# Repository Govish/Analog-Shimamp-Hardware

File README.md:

# Analog Shimamp Hardware
 Hardware and hardware prototypes for a shim amplifier with analog current control

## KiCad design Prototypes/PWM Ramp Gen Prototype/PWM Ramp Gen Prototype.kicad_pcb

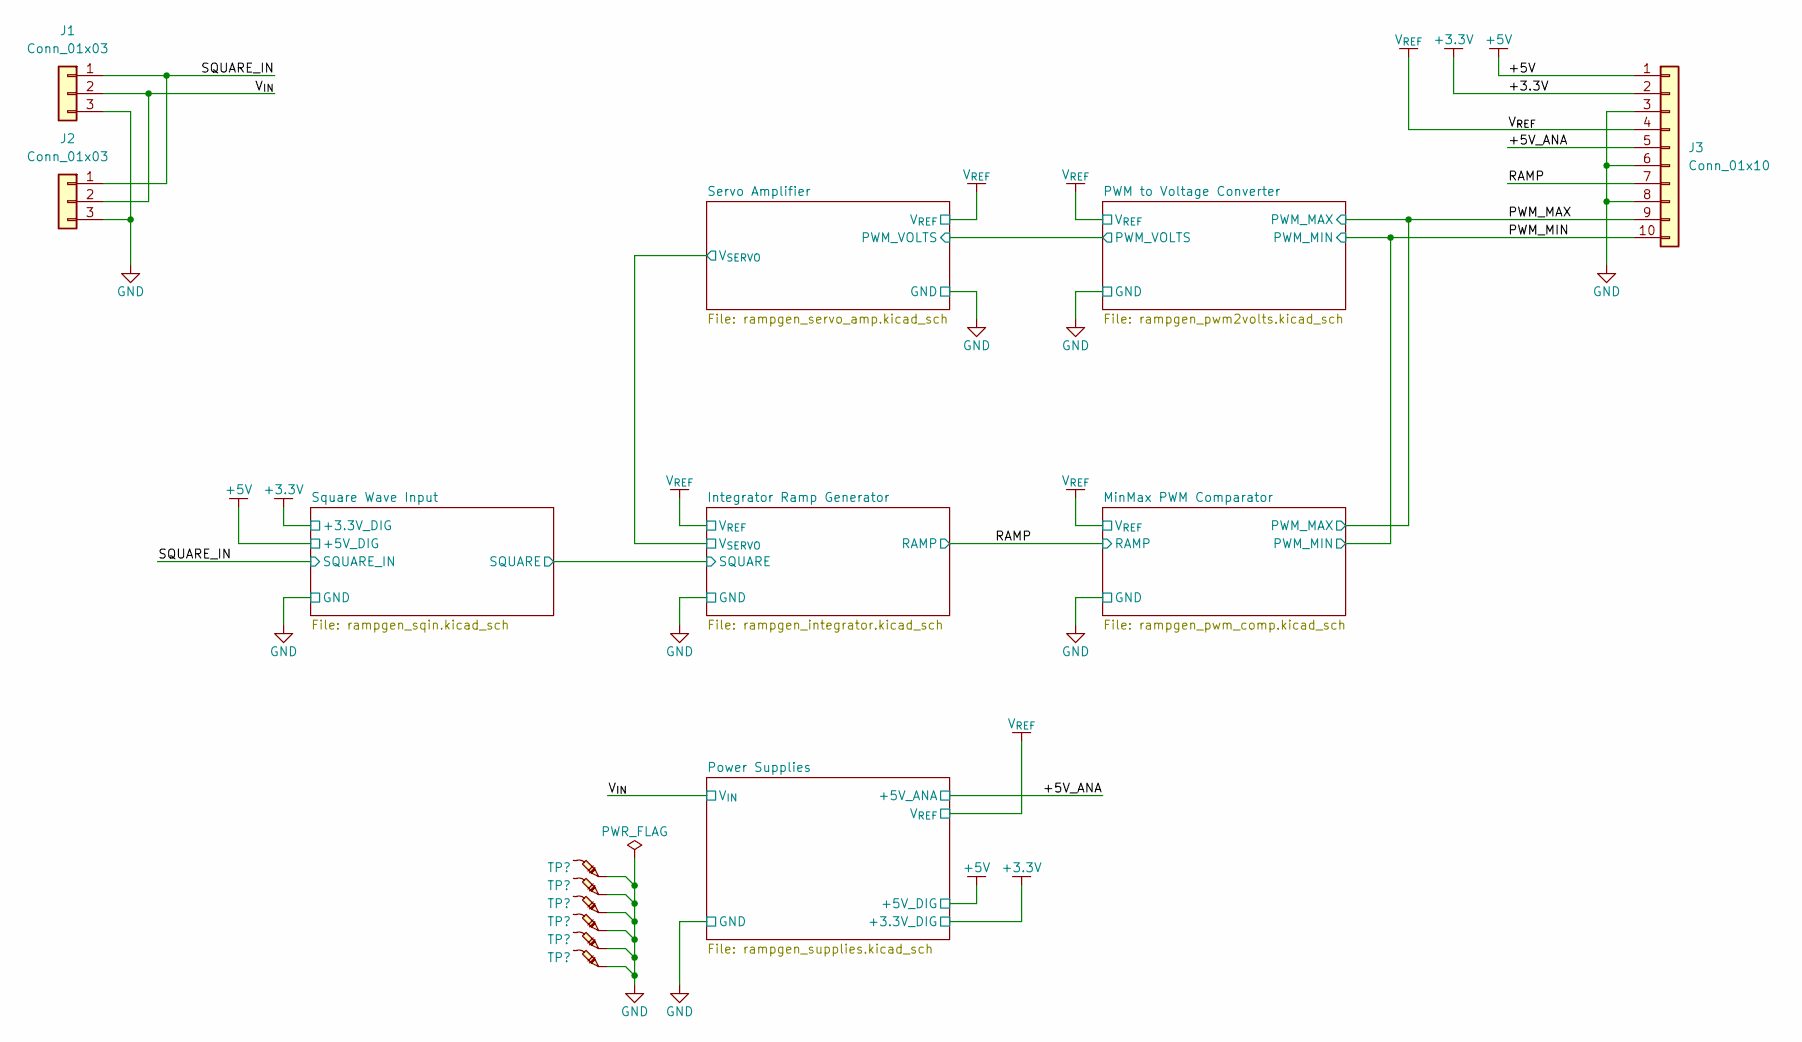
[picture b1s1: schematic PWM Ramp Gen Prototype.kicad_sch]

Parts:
J1, J2: Conn_01x03; PinHeader_1x03_P2.54mm_Vertical
J3: Conn_01x10; PinHeader_1x10_P2.54mm_Vertical
TP1, TP2, TP3, TP4, TP6, TP7: -; TestPoint_Pad_D2.0mm

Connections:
+3.3V: J3.2; also elsewhere on the board
+5V: J3.1; also elsewhere on the board
/+5V_ANA: J3.5; also elsewhere on the board
/PWM_MAX: J3.9; also elsewhere on the board
/PWM_MIN: J3.10; also elsewhere on the board
/RAMP: J3.7; also elsewhere on the board
/SQUARE_IN: J1.1, J2.1; also elsewhere on the board
/V_{IN}: J1.2, J2.2; also elsewhere on the board
GND: J1.3, J2.3, J3.3, J3.6, J3.8, TP1.1, TP2.1, TP3.1, TP4.1, TP6.1, TP7.1; also elsewhere on the board
V_{REF}: J3.4; also elsewhere on the board

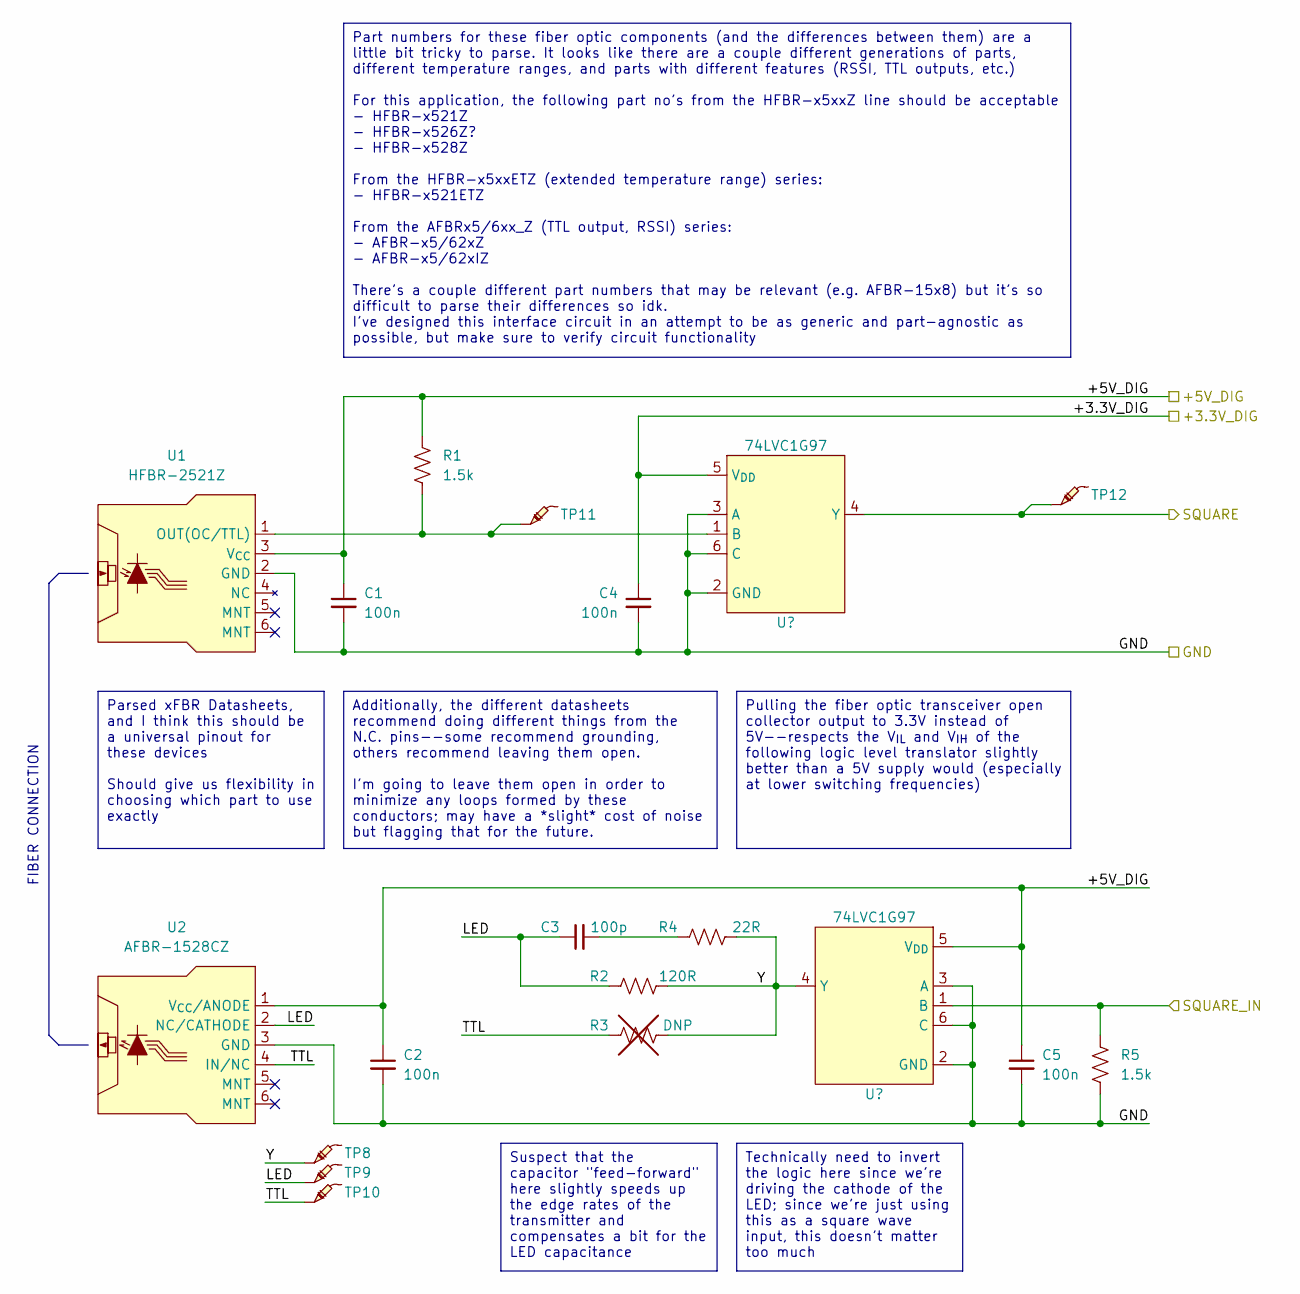
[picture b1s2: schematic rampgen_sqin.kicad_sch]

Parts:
C1, C2, C4, C5: 100n; C_0603_1608Metric_Pad1.08x0.95mm_HandSolder; Part Number CL10B104KB8NNWC
C3: 100p; C_0603_1608Metric_Pad1.08x0.95mm_HandSolder; Part Number GCM1885C2A101JA16D
R1, R5: 1.5k; R_0603_1608Metric_Pad0.98x0.95mm_HandSolder; Part Number RMCF0603FT1K50
R2: 120R; R_0603_1608Metric_Pad0.98x0.95mm_HandSolder; Part Number RMCF0603FT120R
R3: DNP; DNP_R_0603_1608Metric_Pad0.98x0.95mm_HandSolder
R4: 22R; R_0603_1608Metric_Pad0.98x0.95mm_HandSolder; Part Number RMCF0603FT22R0
TP8, TP9, TP10, TP11, TP12: -; TestPoint_Pad_D2.0mm
U1: HFBR-2521Z; Broadcom_xFBR_RX; Part Number HFBR-2521Z
U2: AFBR-1528CZ; Broadcom_xFBR_TX; Part Number AFBR-1528CZ
U3, U4: 74LVC1G97; SOT-363_SC-70-6_Handsoldering; Part Number 74LVC1G97GW,125

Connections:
+3.3V: C4.1, U3.5 (V_{DD}); also elsewhere on the board
+5V: C1.1, C2.1, C5.1, R1.1, U1.3 (V_{CC}), U2.1 (V_{CC}/ANODE), U4.5 (V_{DD}); also elsewhere on the board
/Integrator Ramp Generator/SQUARE: TP12.1, U3.4 (Y); also elsewhere on the board
/SQUARE_IN: R5.1, U4.1 (B); also elsewhere on the board
/Square Wave Input/LED: C3.1, R2.1, TP9.1, U2.2 (NC/CATHODE)
/Square Wave Input/TTL: R3.1, TP10.1, U2.4 (IN/NC)
/Square Wave Input/Y: R2.2, R3.2, R4.2, TP8.1, U4.4 (Y)
GND: C1.2, C2.2, C4.2, C5.2, R5.2, U1.2 (GND), U2.3 (GND), U3.2 (GND), U3.3 (A), U3.6 (C), U4.2 (GND), U4.3 (A), U4.6 (C); also elsewhere on the board
unnamed: C3.2, R4.1
unnamed: R1.2, TP11.1, U1.1 (OUT(OC/TTL)), U3.1 (B)

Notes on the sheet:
Parsed xFBR Datasheets, and I think this should be a universal pinout for these devices Should give us flexibility in choosing which part to use exactly
Part numbers for these fiber optic components (and the differences between them) are a little bit tricky to parse. It looks like there are a couple different generations of parts, different temperature ranges, and parts with different features (RSSI, TTL outputs, etc.) For this application, the fol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
Additionally, the different datasheets recommend doing different things from the N.C. pins--some recommend grounding, others recommend leaving them open. I'm going to leave them open in order to minimize any loops formed by these conductors; may have a *slight* cost of noise but flagging that for t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
Technically need to invert the logic here since we're driving the cathode of the LED; since we're just using this as a square wave input, this doesn't matter too much
Suspect that the capacitor "feed-forward" here slightly speeds up the edge rates of the transmitter and compensates a bit for the LED capacitance
Pulling the fiber optic transceiver open collector output to 3.3V instead of 5V--respects the V_{IL} and V_{IH} of the following logic level translator slightly better than a 5V supply would (especially at lower switching frequencies)
FIBER CONNECTION

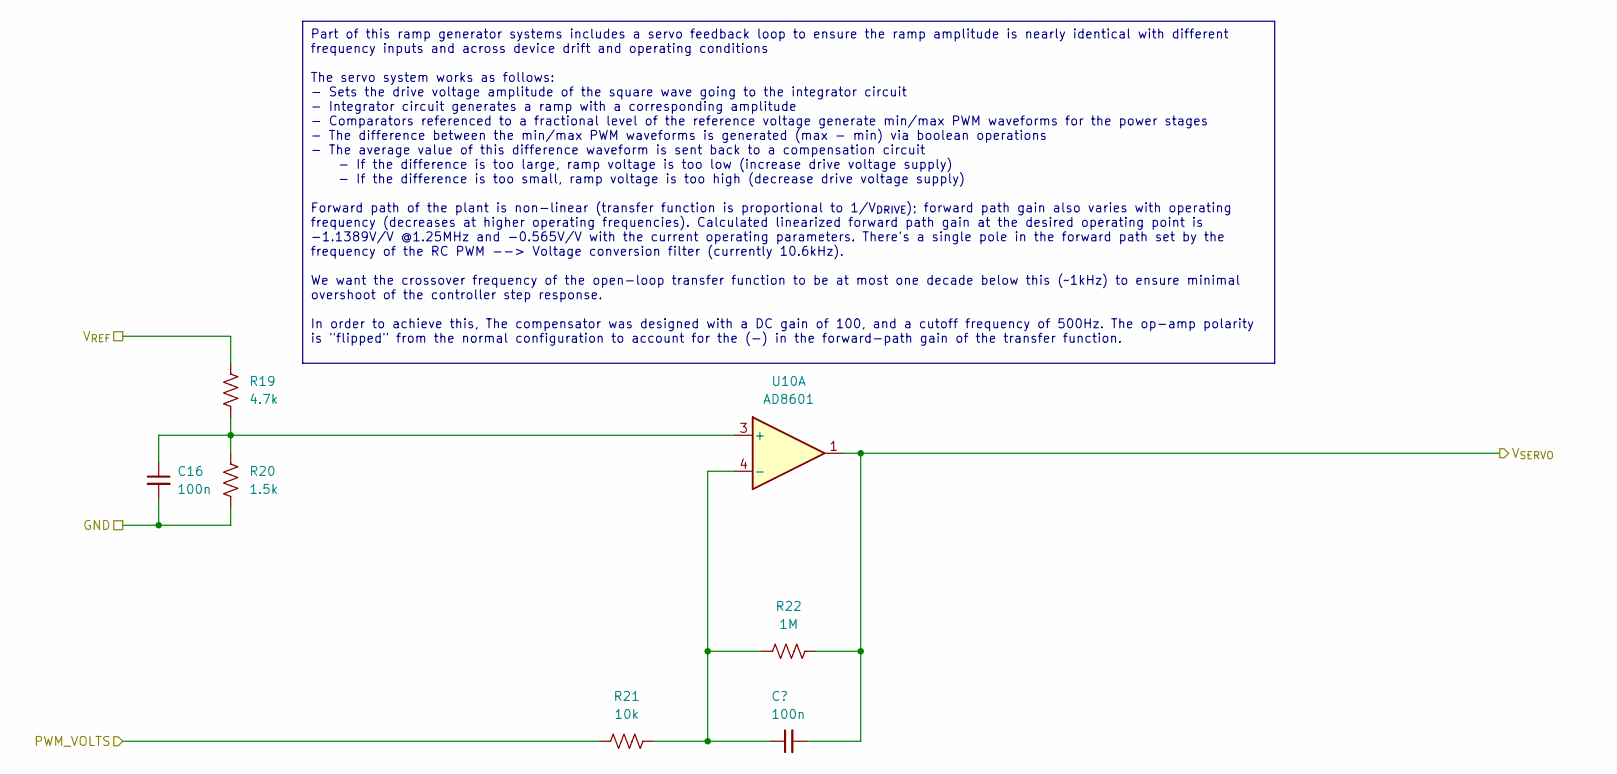
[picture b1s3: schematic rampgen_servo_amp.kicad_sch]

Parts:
C16, C17: 100n; C_0603_1608Metric_Pad1.08x0.95mm_HandSolder; Part Number CL10B104KB8NNWC
R19: 4.7k; R_0603_1608Metric_Pad0.98x0.95mm_HandSolder; Part Number RMCF0603FT4K70
R20: 1.5k; R_0603_1608Metric_Pad0.98x0.95mm_HandSolder; Part Number RMCF0603FT1K50
R21: 10k; R_0603_1608Metric_Pad0.98x0.95mm_HandSolder; Part Number RMCF0603FT10K0
R22: 1M; R_0603_1608Metric_Pad0.98x0.95mm_HandSolder; Part Number RMCF0603FT1M00
U10: AD8601; SOT-23-6_Handsoldering; Part Number AD8601WDRTZ-REEL7

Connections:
/Integrator Ramp Generator/V_{SERVO}: C17.2, R22.2, U10.1; also elsewhere on the board
/PWM to Voltage Converter/PWM_VOLTS: R21.1; also elsewhere on the board
GND: C16.2, R20.2; also elsewhere on the board
unnamed: C16.1, R19.2, R20.1, U10.3 (+)
unnamed: C17.1, R21.2, R22.1, U10.4 (-)
V_{REF}: R19.1; also elsewhere on the board

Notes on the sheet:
Part of this ramp generator systems includes a servo feedback loop to ensure the ramp amplitude is nearly identical with different frequency inputs and across device drift and operating conditions The servo system works as follows: - Sets the drive voltage amplitude of the square wave going to the 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

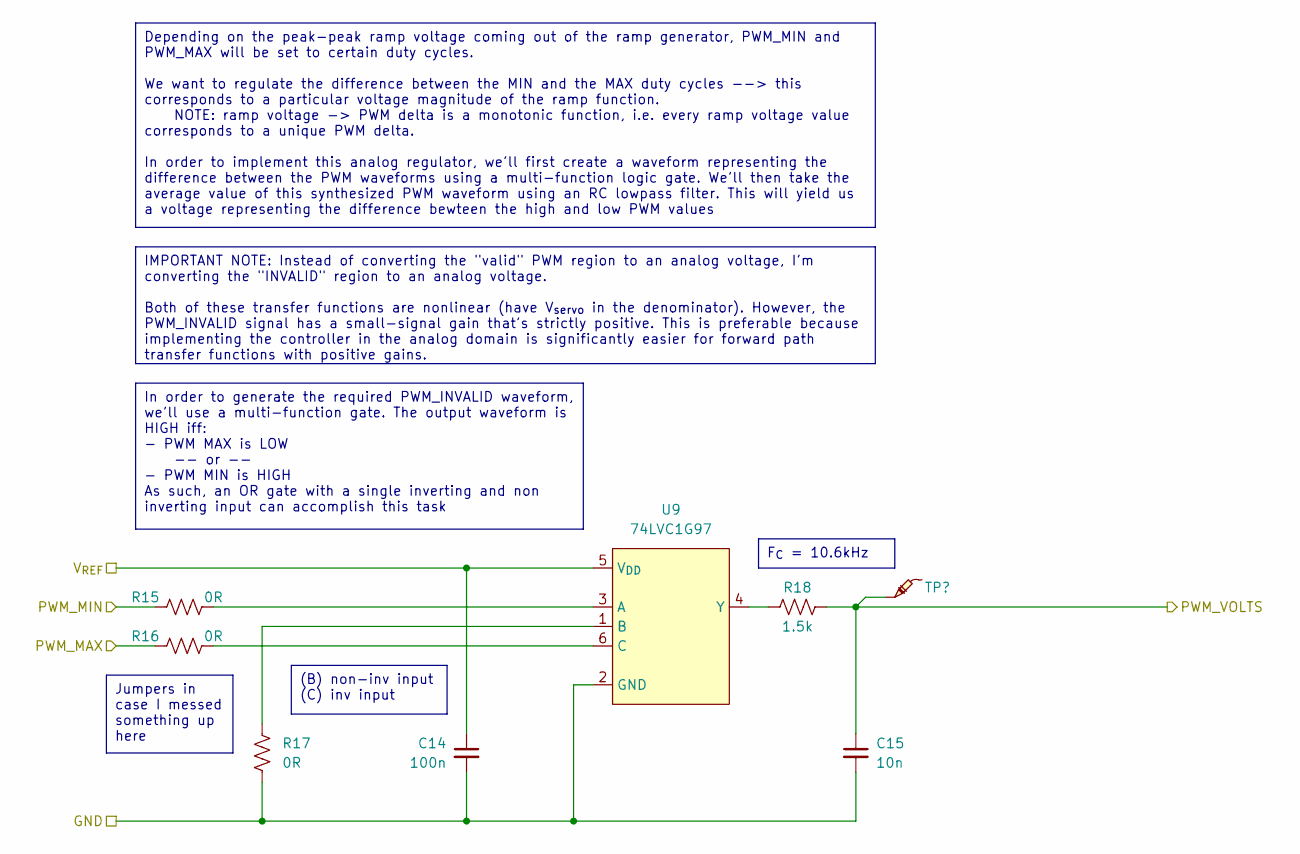
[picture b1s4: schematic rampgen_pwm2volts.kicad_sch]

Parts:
C14: 100n; C_0603_1608Metric_Pad1.08x0.95mm_HandSolder; Part Number CL10B104KB8NNWC
C15: 10n; C_0603_1608Metric_Pad1.08x0.95mm_HandSolder; Part Number CL10B103KB8NNNC
R15, R16, R17: 0R; R_0603_1608Metric_Pad0.98x0.95mm_HandSolder; Part Number RMCF0603ZT0R00
R18: 1.5k; R_0603_1608Metric_Pad0.98x0.95mm_HandSolder; Part Number RMCF0603FT1K50
TP21: -; TestPoint_Pad_D2.0mm
U9: 74LVC1G97; SOT-363_SC-70-6_Handsoldering; Part Number 74LVC1G97GW,125

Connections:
/PWM to Voltage Converter/PWM_VOLTS: C15.1, R18.2, TP21.1; also elsewhere on the board
/PWM_MAX: R16.1; also elsewhere on the board
/PWM_MIN: R15.1; also elsewhere on the board
GND: C14.2, C15.2, R17.2, U9.2 (GND); also elsewhere on the board
unnamed: R15.2, U9.3 (A)
unnamed: R17.1, U9.1 (B)
unnamed: R16.2, U9.6 (C)
unnamed: R18.1, U9.4 (Y)
V_{REF}: C14.1, U9.5 (V_{DD}); also elsewhere on the board

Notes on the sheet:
IMPORTANT NOTE: Instead of converting the "valid" PWM region to an analog voltage, I'm converting the "INVALID" region to an analog voltage. Both of these transfer functions are nonlinear (have V_{servo} in the denominator). However, the PWM_INVALID signal has a small-signal gain that's strictly po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
Depending on the peak-peak ramp voltage coming out of the ramp generator, PWM_MIN and PWM_MAX will be set to certain duty cycles. We want to regulate the difference between the MIN and the MAX duty cycles --> this corresponds to a particular voltage magnitude of the ramp function. NOTE: ramp voltag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
F_{C} = 10.6kHz
In order to generate the required PWM_INVALID waveform, we'll use a multi-function gate. The output waveform is HIGH iff: - PWM MAX is LOW -- or -- - PWM MIN is HIGH As such, an OR gate with a single inverting and non inverting input can accomplish this task
(B) non-inv input (C) inv input
Jumpers in case I messed something up here

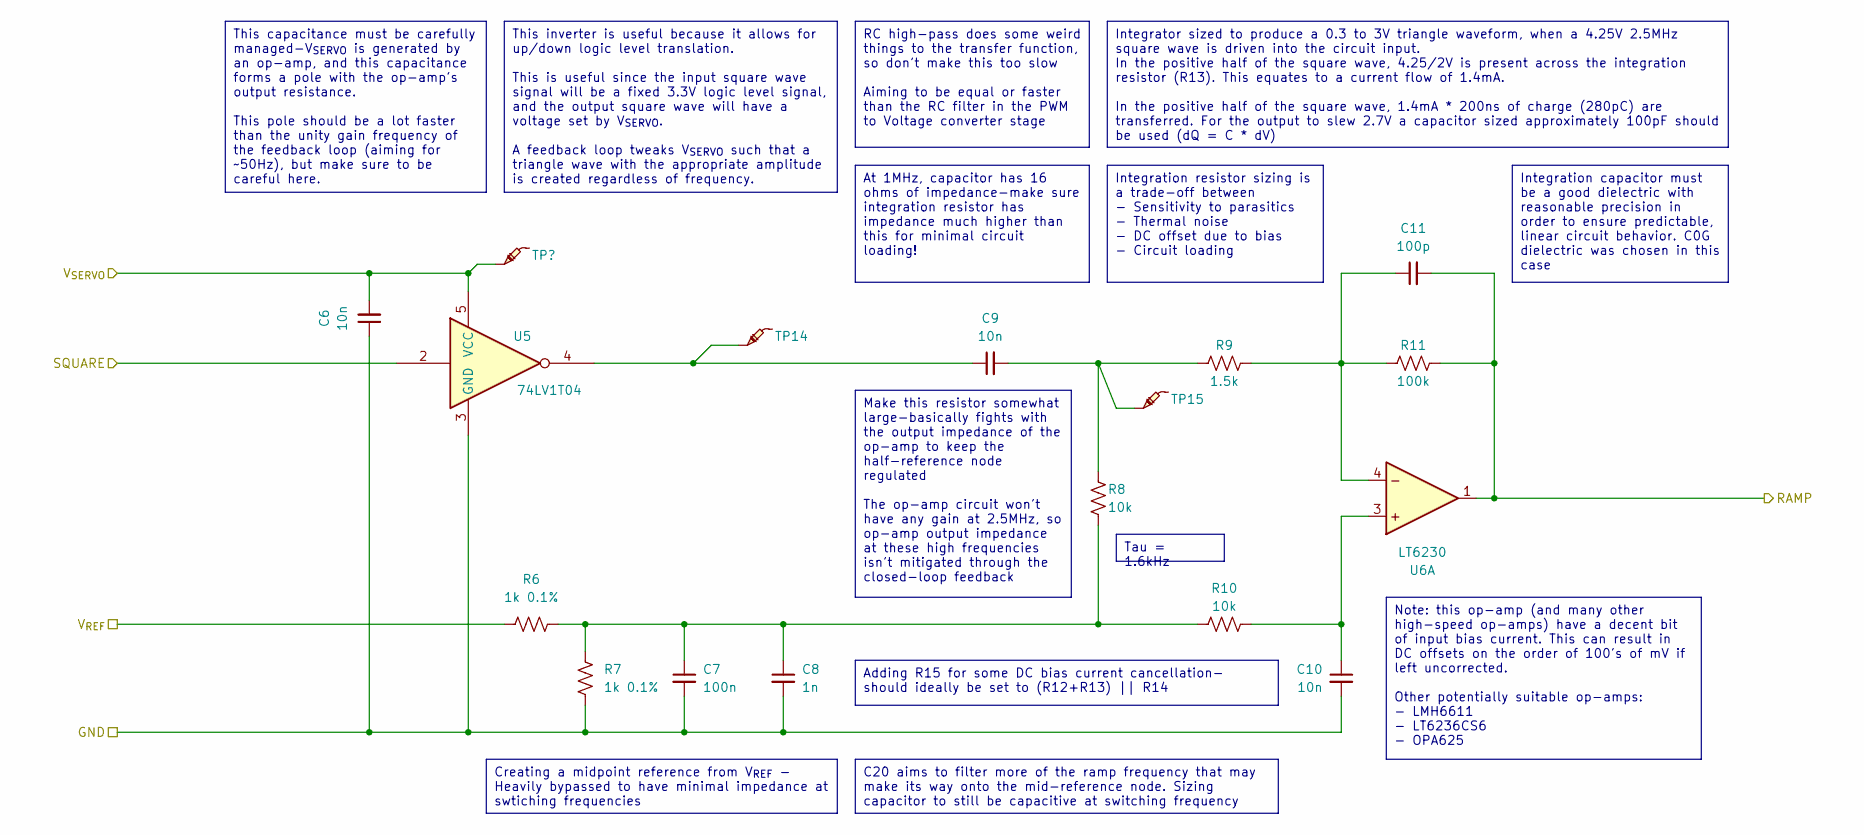
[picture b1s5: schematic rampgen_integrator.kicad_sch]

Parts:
C6, C9, C10: 10n; C_0603_1608Metric_Pad1.08x0.95mm_HandSolder; Part Number CL10B103KB8NNNC
C7: 100n; C_0603_1608Metric_Pad1.08x0.95mm_HandSolder; Part Number CL10B104KB8NNWC
C8: 1n; C_0603_1608Metric_Pad1.08x0.95mm_HandSolder; Part Number CL10B102KB8NNNC
C11: 100p; C_0603_1608Metric_Pad1.08x0.95mm_HandSolder; Part Number GCM1885C2A101JA16D
R6, R7: 1k 0.1%; R_0603_1608Metric_Pad0.98x0.95mm_HandSolder; Part Number RNCF0603BTE1K00
R8, R10: 10k; R_0603_1608Metric_Pad0.98x0.95mm_HandSolder; Part Number RMCF0603FT10K0
R9: 1.5k; R_0603_1608Metric_Pad0.98x0.95mm_HandSolder; Part Number RMCF0603FT1K50
R11: 100k; R_0603_1608Metric_Pad0.98x0.95mm_HandSolder; Part Number RMCF0603FT100K
TP13, TP14, TP15: -; TestPoint_Pad_D2.0mm
U5: 74LV1T04; SOT-23-5_HandSoldering; Part Number SN74LV1T04DBVR
U6: LT6230; TSOT-23-6; Part Number LT6230CS6#TRPBF

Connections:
/Integrator Ramp Generator/SQUARE: U5.2; also elsewhere on the board
/Integrator Ramp Generator/V_{SERVO}: C6.2, TP13.1, U5.5 (VCC); also elsewhere on the board
/RAMP: C11.2, R11.2, U6.1; also elsewhere on the board
GND: C6.1, C7.2, C8.2, C10.2, R7.1, U5.3 (GND); also elsewhere on the board
unnamed: C7.1, C8.1, R6.2, R7.2, R8.2, R10.1
unnamed: C9.1, TP14.1, U5.4
unnamed: C9.2, R8.1, R9.1, TP15.1
unnamed: C10.1, R10.2, U6.3
unnamed: C11.1, R9.2, R11.1, U6.4
V_{REF}: R6.1; also elsewhere on the board

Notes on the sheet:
RC high-pass does some weird things to the transfer function, so don't make this too slow Aiming to be equal or faster than the RC filter in the PWM to Voltage converter stage
Integration resistor sizing is a trade-off between - Sensitivity to parasitics - Thermal noise - DC offset due to bias - Circuit loading
At 1MHz, capacitor has 16 ohms of impedance-make sure integration resistor has impedance much higher than this for minimal circuit loading!
Integrator sized to produce a 0.3 to 3V triangle waveform, when a 4.25V 2.5MHz square wave is driven into the circuit input. In the positive half of the square wave, 4.25/2V is present across the integration resistor (R13). This equates to a current flow of 1.4mA. In the positive half of the square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
This inverter is useful because it allows for up/down logic level translation. This is useful since the input square wave signal will be a fixed 3.3V logic level signal, and the output square wave will have a voltage set by V_{SERVO}. A feedback loop tweaks V_{SERVO} such that a triangle wave with 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
Creating a midpoint reference from V_{REF} - Heavily bypassed to have minimal impedance at swtiching frequencies
Tau = 1.6kHz
Note: this op-amp (and many other high-speed op-amps) have a decent bit of input bias current. This can result in DC offsets on the order of 100's of mV if left uncorrected. Other potentially suitable op-amps: - LMH6611 - LT6236CS6 - OPA625
Integration capacitor must be a good dielectric with reasonable precision in order to ensure predictable, linear circuit behavior. C0G dielectric was chosen in this case
This capacitance must be carefully managed-V_{SERVO} is generated by an op-amp, and this capacitance forms a pole with the op-amp's output resistance. This pole should be a lot faster than the unity gain frequency of the feedback loop (aiming for ~50Hz), but make sure to be careful here.
C20 aims to filter more of the ramp frequency that may make its way onto the mid-reference node. Sizing capacitor to still be capacitive at switching frequency
Adding R15 for some DC bias current cancellation- should ideally be set to (R12+R13) || R14
Make this resistor somewhat large-basically fights with the output impedance of the op-amp to keep the half-reference node regulated The op-amp circuit won't have any gain at 2.5MHz, so op-amp output impedance at these high frequencies isn't mitigated through the closed-loop feedback

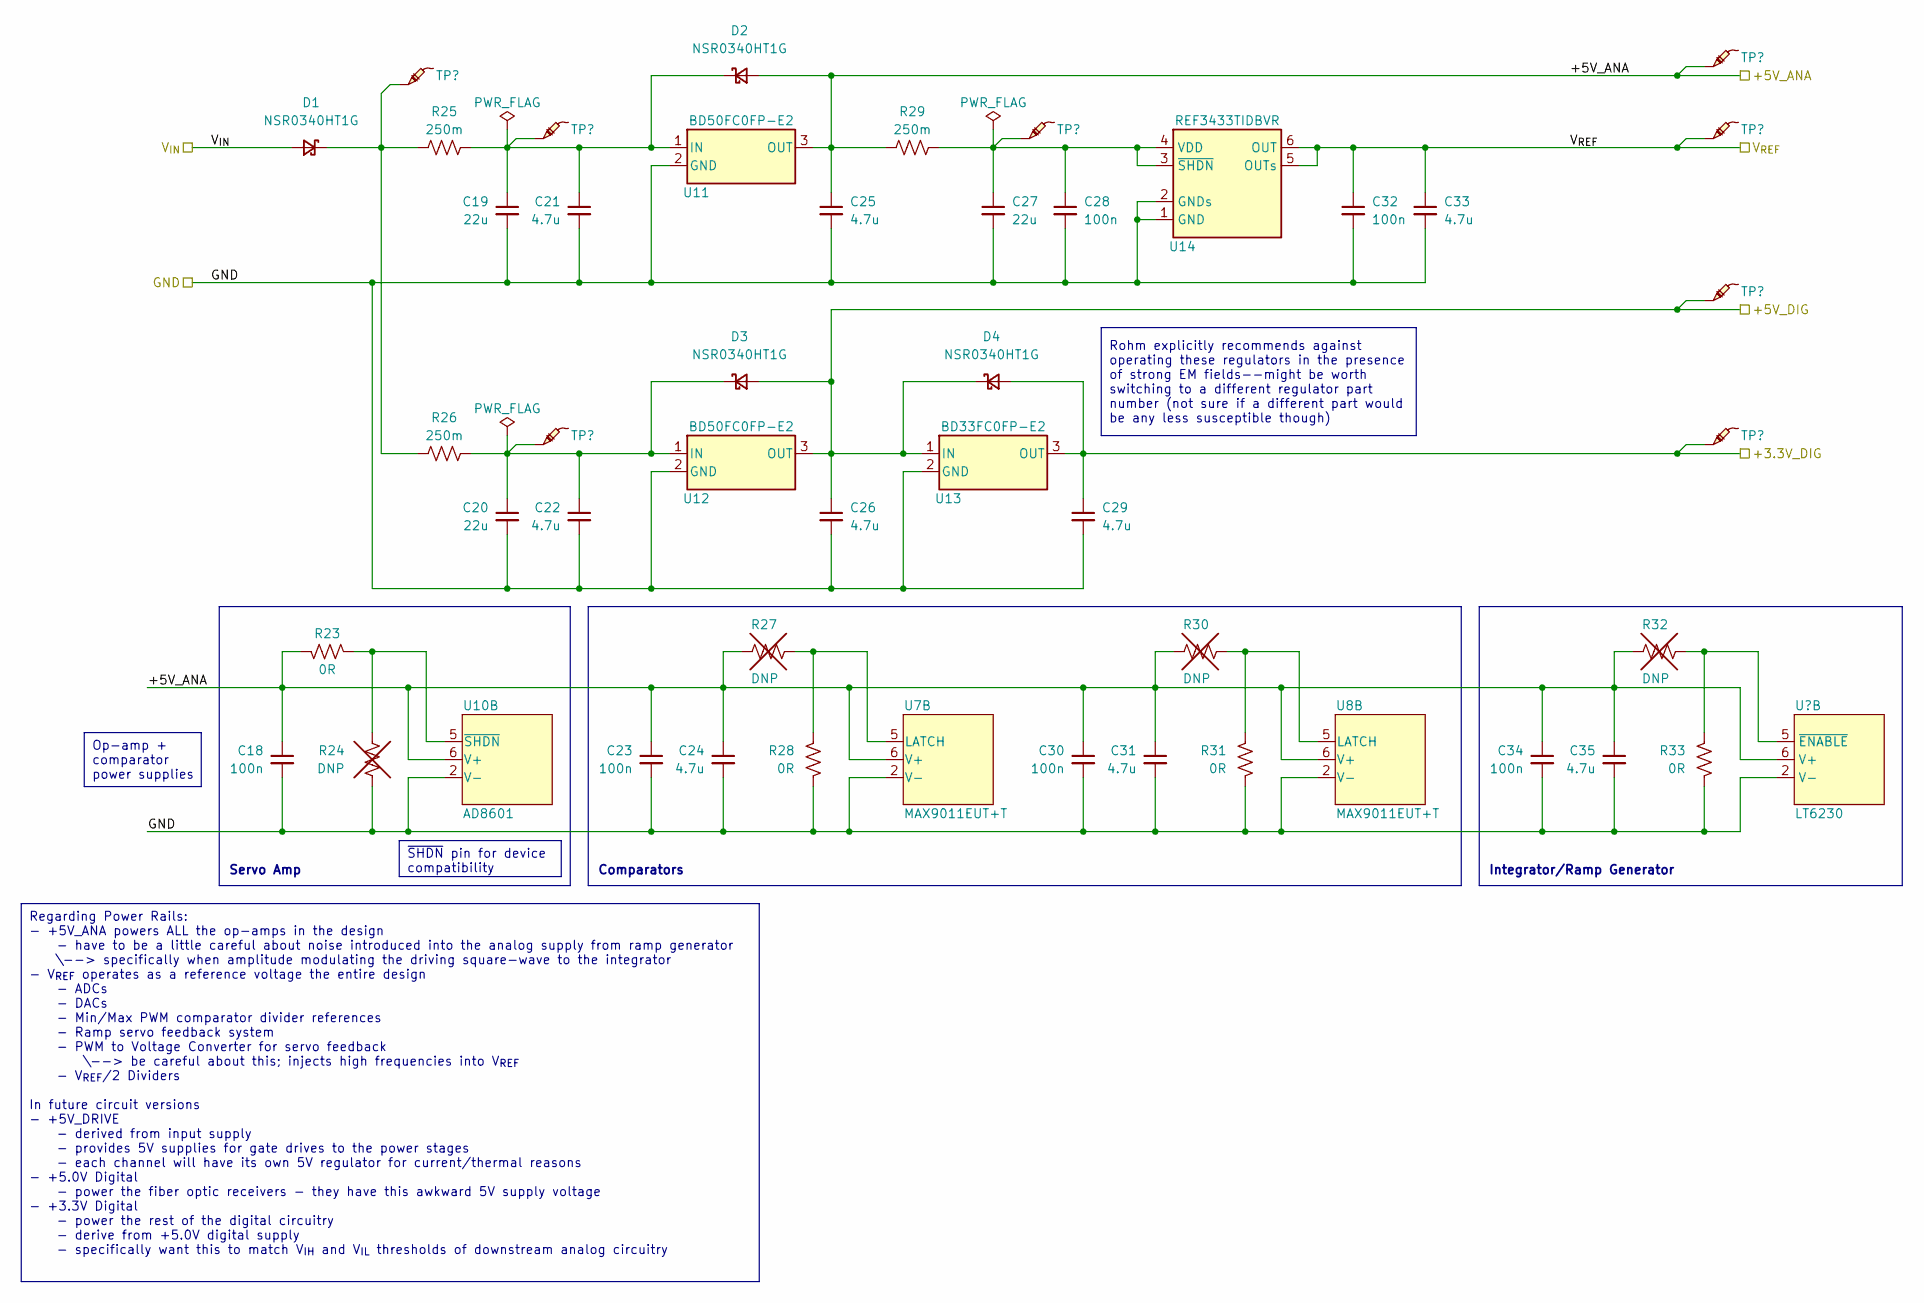
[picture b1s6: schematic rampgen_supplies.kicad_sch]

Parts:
C18, C23, C28, C30, C32, C34: 100n; C_0603_1608Metric_Pad1.08x0.95mm_HandSolder; Part Number CL10B104KB8NNWC
C19, C20, C27: 22u; C_1210_3225Metric_Pad1.33x2.70mm_HandSolder; Part Number CL32B226KAJNNNE
C21, C22, C24, C25, C26, C29, C31, C33, C35: 4.7u; C_0805_2012Metric_Pad1.18x1.45mm_HandSolder; Part Number CL21A475KLCLQNC
D1, D2, D3, D4: NSR0340HT1G; D_SOD-323_HandSoldering; Part Number NSR0340HT1G
R23, R28, R31, R33: 0R; R_0603_1608Metric_Pad0.98x0.95mm_HandSolder; Part Number RMCF0603ZT0R00
R24, R27, R30, R32: DNP; DNP_R_0603_1608Metric_Pad0.98x0.95mm_HandSolder
R25, R26, R29: 250m; R_1206_3216Metric_Pad1.30x1.75mm_HandSolder; Part Number CSR1206FKR250
TP22, TP23, TP24, TP25, TP26, TP27, TP28, TP29: -; TestPoint_Pad_D2.0mm
U6: LT6230; TSOT-23-6; Part Number LT6230CS6#TRPBF
U7, U8: MAX9011EUT+T; SOT-23-6_Handsoldering; Part Number MAX9011EUT+T
U10: AD8601; SOT-23-6_Handsoldering; Part Number AD8601WDRTZ-REEL7
U11, U12: BD50FC0FP-E2; TO-252-2; Part Number BD50FC0FP-E2
U13: BD33FC0FP-E2; TO-252-2; Part Number BD33FC0FP-E2
U14: REF3433TIDBVR; SOT-23-6; Part Number REF3433TIDBVR

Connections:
+3.3V: C29.1, D4.2 (A), TP29.1, U13.3 (OUT); also elsewhere on the board
+5V: C26.1, D3.2 (A), D4.1 (K), TP28.1, U12.3 (OUT), U13.1 (IN); also elsewhere on the board
/+5V_ANA: C18.1, C23.1, C24.1, C25.1, C30.1, C31.1, C34.1, C35.1, D2.2 (A), R23.2, R27.1, R29.1, R30.1, R32.1, TP26.1, U6.6 (V+), U7.6 (V+), U8.6 (V+), U10.6 (V+), U11.3 (OUT); also elsewhere on the board
/V_{IN}: D1.2 (A); also elsewhere on the board
GND: C18.2, C19.2, C20.2, C21.2, C22.2, C23.2, C24.2, C25.2, C26.2, C27.2, C28.2, C29.2, C30.2, C31.2, C32.2, C33.2, C34.2, C35.2, R24.2, R28.1, R31.1, R33.1, U6.2 (V-), U7.2 (V-), U8.2 (V-), U10.2 (V-), U11.2 (GND), U12.2 (GND), U13.2 (GND), U14.1 (GND), U14.2 (GNDs); also elsewhere on the board
unnamed: D1.1 (K), R25.1, R26.1, TP22.1
unnamed: C19.1, C21.1, D2.1 (K), R25.2, TP23.1, U11.1 (IN)
unnamed: C20.1, C22.1, D3.1 (K), R26.2, TP24.1, U12.1 (IN)
unnamed: R32.2, R33.2, U6.5 (~ENABLE)
unnamed: R27.2, R28.2, U7.5 (LATCH)
unnamed: R30.2, R31.2, U8.5 (LATCH)
unnamed: R23.1, R24.1, U10.5 (~SHDN)
unnamed: C27.1, C28.1, R29.2, TP25.1, U14.3 (~SHDN), U14.4 (VDD)
V_{REF}: C32.1, C33.1, TP27.1, U14.5 (OUTs), U14.6 (OUT); also elsewhere on the board

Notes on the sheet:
Rohm explicitly recommends against operating these regulators in the presence of strong EM fields--might be worth switching to a different regulator part number (not sure if a different part would be any less susceptible though)
Regarding Power Rails: - +5V_ANA powers ALL the op-amps in the design - have to be a little careful about noise introduced into the analog supply from ramp generator \--> specifically when amplitude modulating the driving square-wave to the integrator - V_{REF} operates as a reference voltage the e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
~{SHDN} pin for device compatibility
Op-amp + comparator power supplies
Servo Amp
Integrator/Ramp Generator
Comparators

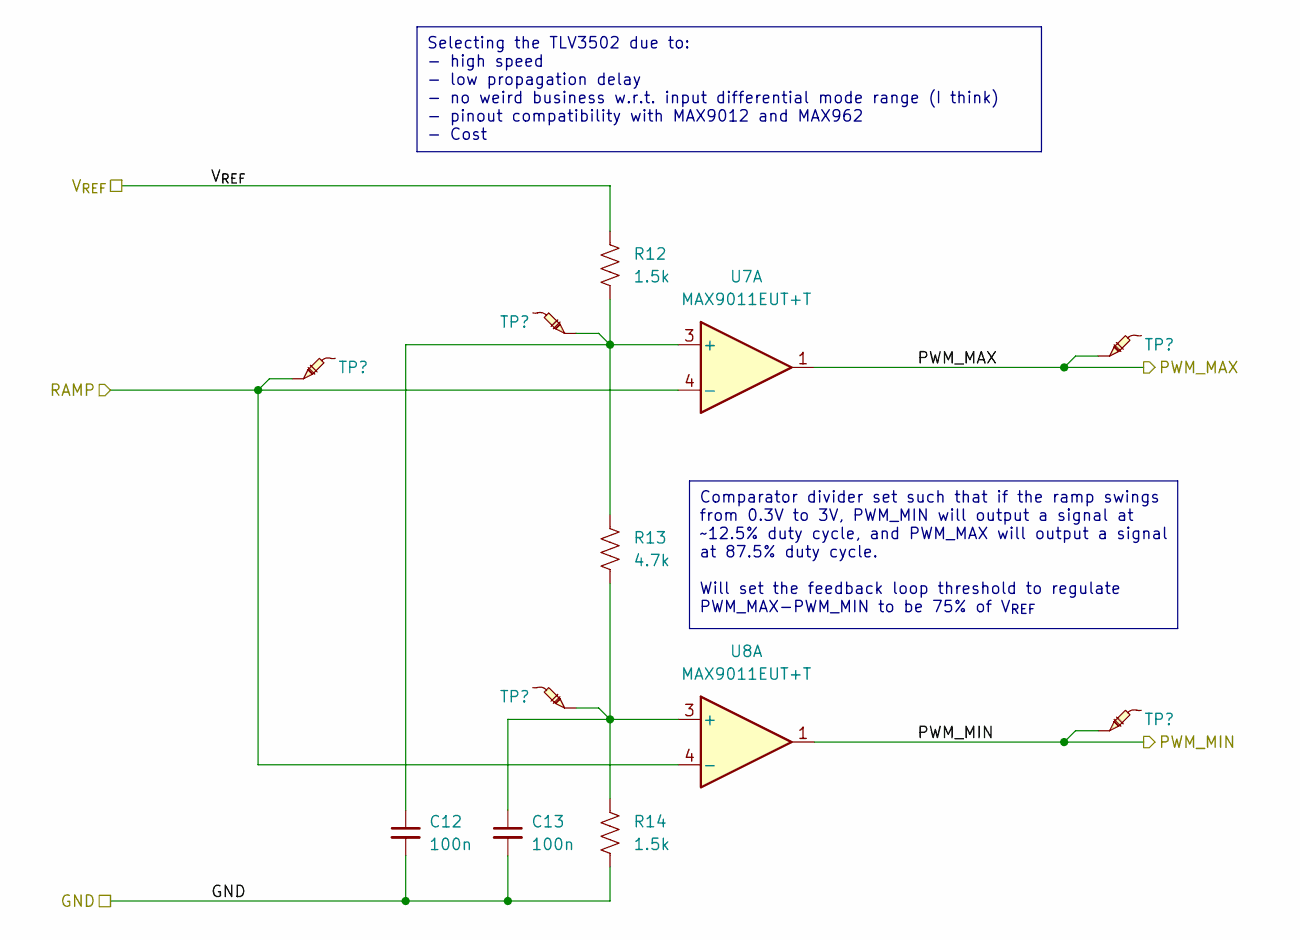
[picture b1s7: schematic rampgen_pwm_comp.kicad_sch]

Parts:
C12, C13: 100n; C_0603_1608Metric_Pad1.08x0.95mm_HandSolder; Part Number CL10B104KB8NNWC
R12, R14: 1.5k; R_0603_1608Metric_Pad0.98x0.95mm_HandSolder; Part Number RMCF0603FT1K50
R13: 4.7k; R_0603_1608Metric_Pad0.98x0.95mm_HandSolder; Part Number RMCF0603FT4K70
TP16, TP17, TP18, TP19, TP20: -; TestPoint_Pad_D2.0mm
U7, U8: MAX9011EUT+T; SOT-23-6_Handsoldering; Part Number MAX9011EUT+T

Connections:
/PWM_MAX: TP19.1, U7.1; also elsewhere on the board
/PWM_MIN: TP20.1, U8.1; also elsewhere on the board
/RAMP: TP16.1, U7.4 (-), U8.4 (-); also elsewhere on the board
GND: C12.2, C13.2, R14.2; also elsewhere on the board
unnamed: C12.1, R12.2, R13.1, TP17.1, U7.3 (+)
unnamed: C13.1, R13.2, R14.1, TP18.1, U8.3 (+)
V_{REF}: R12.1; also elsewhere on the board

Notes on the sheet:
Selecting the TLV3502 due to: - high speed - low propagation delay - no weird business w.r.t. input differential mode range (I think) - pinout compatibility with MAX9012 and MAX962 - Cost
Comparator divider set such that if the ramp swings from 0.3V to 3V, PWM_MIN will output a signal at ~12.5% duty cycle, and PWM_MAX will output a signal at 87.5% duty cycle. Will set the feedback loop threshold to regulate PWM_MAX-PWM_MIN to be 75% of V_{REF}

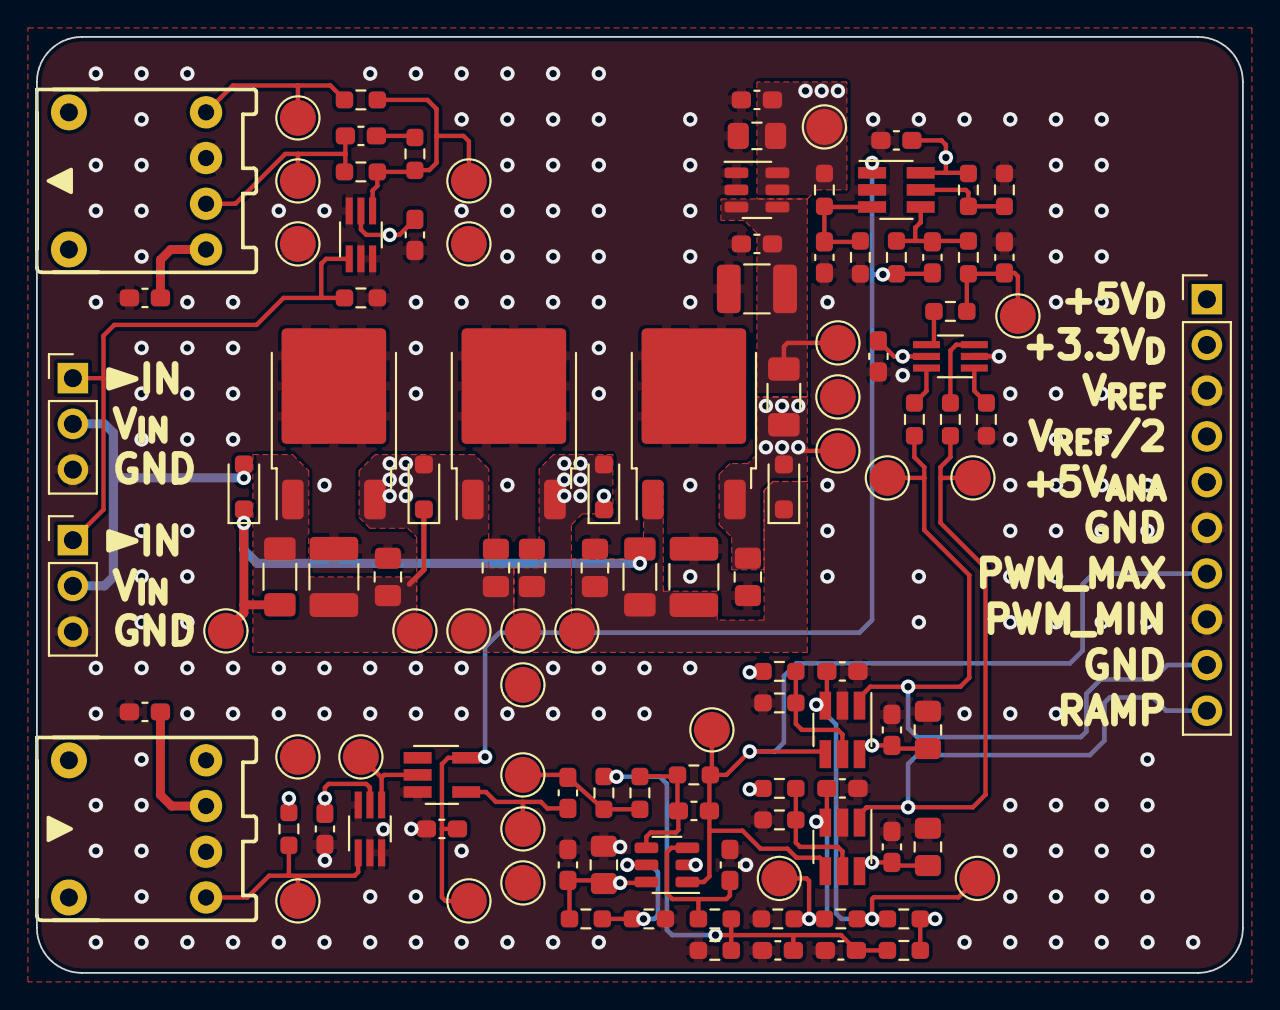
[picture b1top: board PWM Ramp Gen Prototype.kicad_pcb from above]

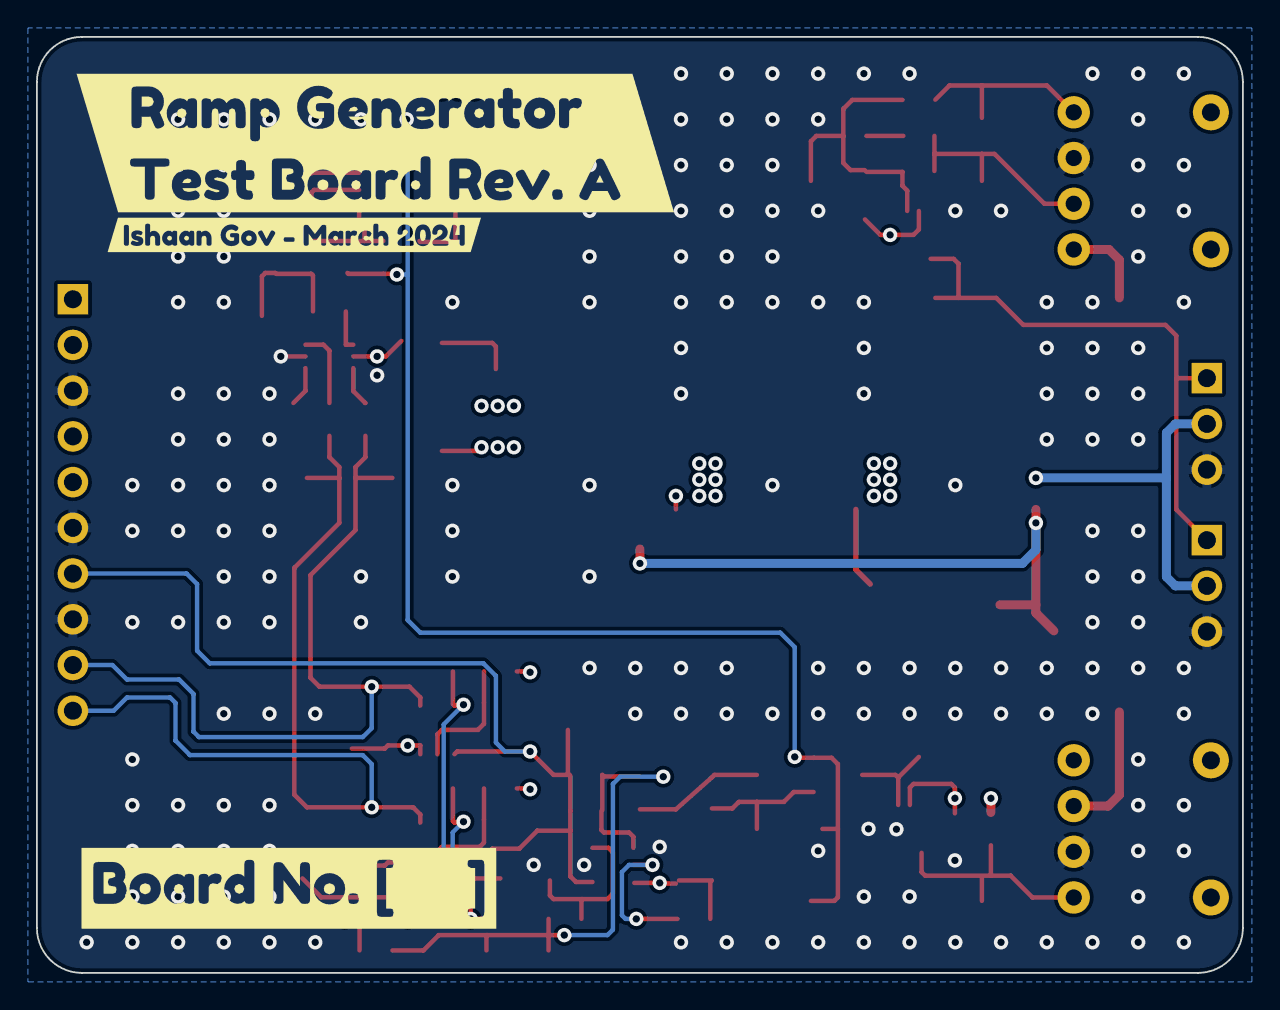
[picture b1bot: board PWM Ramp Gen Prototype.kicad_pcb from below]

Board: 4 copper layers, 67.0 x 52.0 mm, 120 parts (3 on the bottom side), 39 nets.

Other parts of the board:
kibuzzard-65FA71D7: G***; kibuzzard-65FA71D7
kibuzzard-65FA722F: G***; kibuzzard-65FA722F
kibuzzard-65FA7252: G***; kibuzzard-65FA7252

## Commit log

2024-03-19 Finishing ramp generator schematic, starting layout
2024-03-19 Adding PDF version of schematic
2024-03-20 Finishing layout
2024-03-21 Comparator and Op-amp tweaks for BOM consolidation; final layout
2024-03-21 Fix minor footprint update issues
2024-03-21 updating gerbers
2024-04-05 Digital Interface Prototype First Steps
